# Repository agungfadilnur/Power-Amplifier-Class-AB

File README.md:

## Power Amplifier Class AB

This Drivers use SOCL (Super Output Capacitor Less) 506 and use 8 Pair Transistor for final output 

*Testing Video*

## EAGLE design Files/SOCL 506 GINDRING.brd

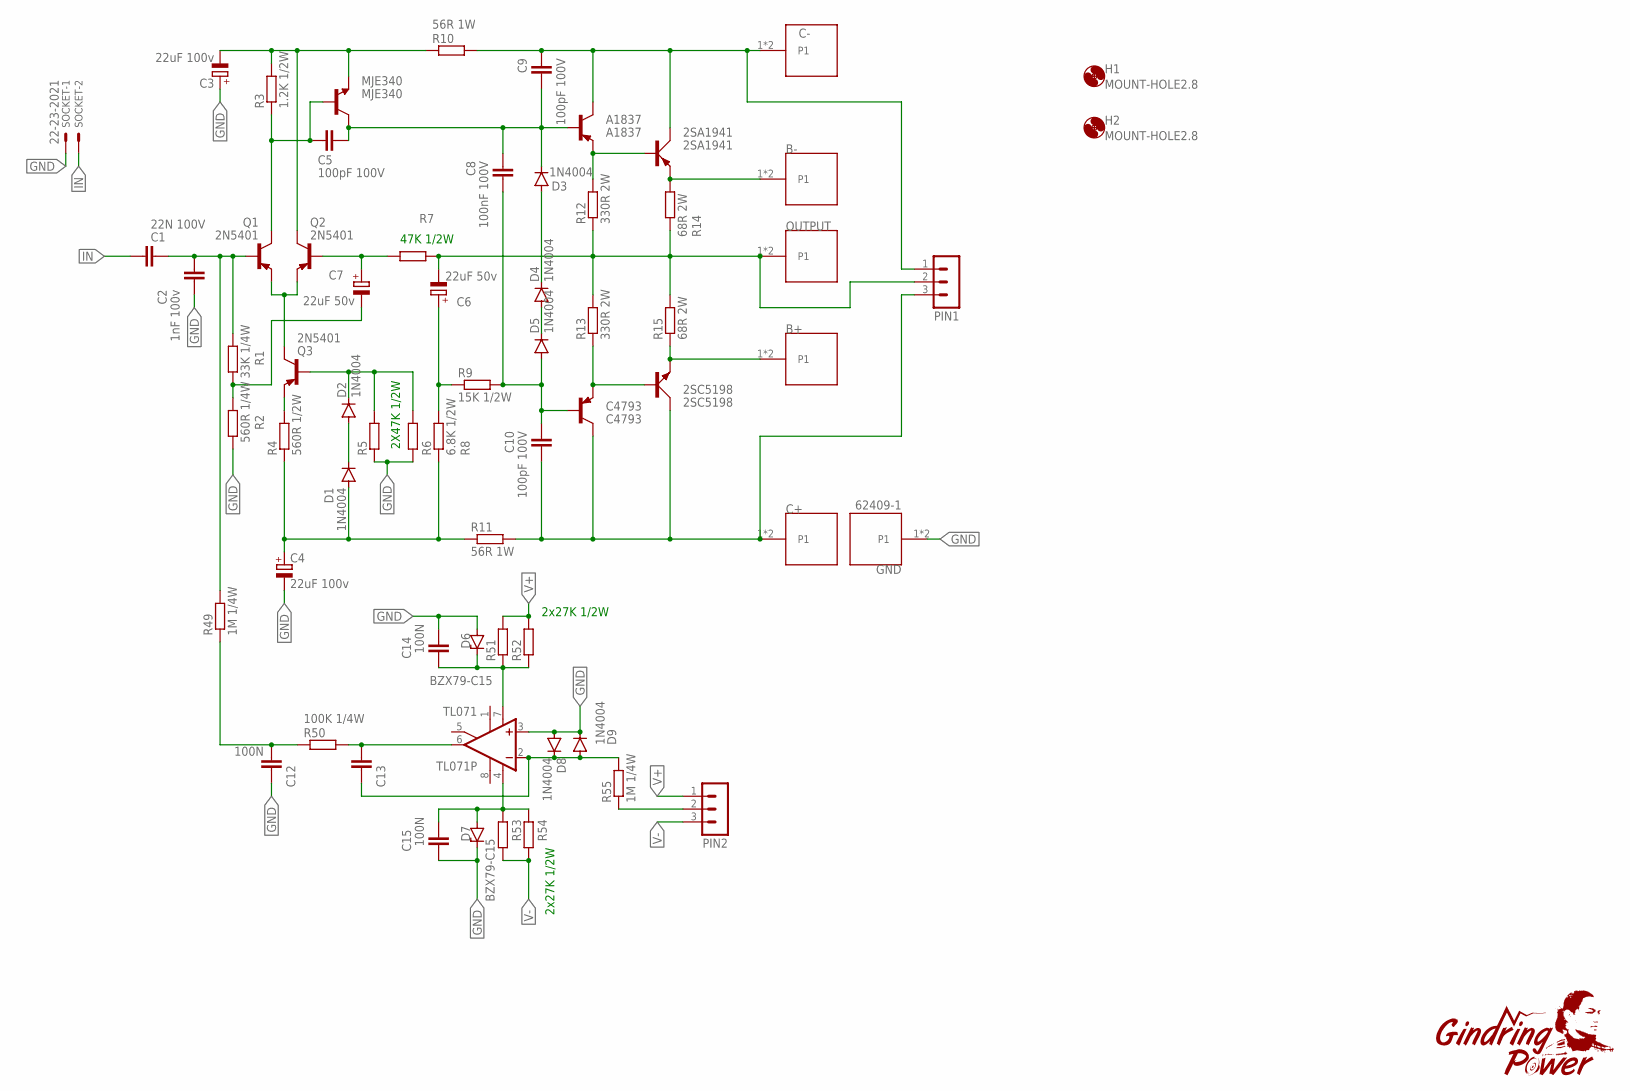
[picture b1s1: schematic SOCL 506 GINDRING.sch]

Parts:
2SA1941: 2SA1941; TOP3AV
2SC5198: 2SC5198; TOP3AV
A1837: A1837; TO220V
B+: 62409-1; TE_62409-1
B-: 62409-1; TE_62409-1
C1: 22N 100V; C5B2.5
C2: 1nF 100v; C5B2.5
C3, C4: 22uF 100v; E3,5-8
C5, C9, C10: 100pF 100V; C5B2.5
C6, C7: 22uF 50v; E2,5-6E
C8: 100nF 100V; C5B2.5
C12, C13, C14, C15: 100N; C5B2.5
C4793: C4793; TO220V
C+: 62409-1; TE_62409-1
C-: 62409-1; TE_62409-1
D1, D2, D3, D4, D5, D8, D9: 1N4004; DO41-10
D6, D7: BZX79-C15; DO41Z10
GND: 62409-1; TE_62409-1
H1, H2: MOUNT-HOLE2.8; 2,8
MJE340: MJE340; TO126
OUTPUT: 62409-1; TE_62409-1
PIN1, PIN2: MA03-1
Q1, Q2, Q3: 2N5401; TO92-CBE
R1: 33K 1/4W; 0207/10
R2: 560R 1/4W; 0207/10
R3: 1.2K 1/2W; 0207/15
R4: 560R 1/2W; 0207/15
R5, R6, R7, R51, R52, R53, R54: R-EU_0207/15; 0207/15
R8: 6.8K 1/2W; 0207/15
R9: 15K 1/2W; 0207/15
R10, R11: 56R 1W; 0207/15
R12, R13: 330R 2W; 0207/15
R14, R15: 68R 2W; 0207/15
R49, R55: 1M 1/4W; 0207/10
R50: 100K 1/4W; 0207/10
SOCKET: 22-23-2021
TL071: TL071P; DIL08

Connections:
GND: C2.2, C3.+, C4.-, C12.1, C14.2, C15.1, D6.A, D7.C, D8.A, D9.C, GND.1, GND.2, R2.1, R5.1, R6.1, SOCKET.1, TL071.3 (+IN)
IN: C1.1, SOCKET.2
unnamed: C1.2, C2.1, Q1.B, R1.2, R49.2
unnamed: Q1.E, Q2.E, Q3.C
unnamed: C5.1, MJE340.3 (B), Q1.C, R3.1
unnamed: C7.-, R1.1, R2.2
unnamed: C3.-, MJE340.1 (E), Q2.C, R3.2, R10.1
unnamed: Q3.E, R4.2
unnamed: D2.C, Q3.B, R5.2, R6.2
unnamed: D1.C, D2.A
unnamed: C4.+, D1.A, R4.1, R8.1, R11.1
unnamed: C7.+, Q2.B, R7.1
unnamed: 2SC5198.B, C4793.3 (E), R13.1
unnamed: C6.-, OUTPUT.1, OUTPUT.2, PIN1.2, R7.2, R12.1, R13.2, R14.1, R15.2
unnamed: C6.+, R8.2, R9.1
unnamed: C8.1, C10.2, C4793.1 (B), D5.A, R9.2
unnamed: 2SA1941.C, A1837.2 (C), C9.2, C-.1, C-.2, PIN1.1, R10.2
unnamed: A1837.1 (B), C5.2, C8.2, C9.1, D3.C, MJE340.2 (C)
unnamed: D3.A, D4.C
unnamed: D4.A, D5.C
unnamed: 2SC5198.C, C10.1, C4793.2 (C), C+.1, C+.2, PIN1.3, R11.2
unnamed: 2SA1941.B, A1837.3 (E), R12.2
unnamed: 2SA1941.E, B-.1, B-.2, R14.2
unnamed: C12.2, R49.1, R50.1
unnamed: 2SC5198.E, B+.1, B+.2, R15.1
unnamed: C14.1, D6.C, R51.1, R52.1, TL071.7 (V+)
unnamed: C13.1, D8.C, D9.A, R55.2, TL071.2 (-IN)
unnamed: C15.2, D7.A, R53.2, R54.2, TL071.4 (V-)
unnamed: C13.2, R50.2, TL071.6 (OUT)
unnamed: PIN2.2, R55.1
V+: PIN2.1, R51.2, R52.2
V-: PIN2.3, R53.1, R54.1

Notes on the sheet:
2X47K 1/2W
47K 1/2W
2x27K 1/2W

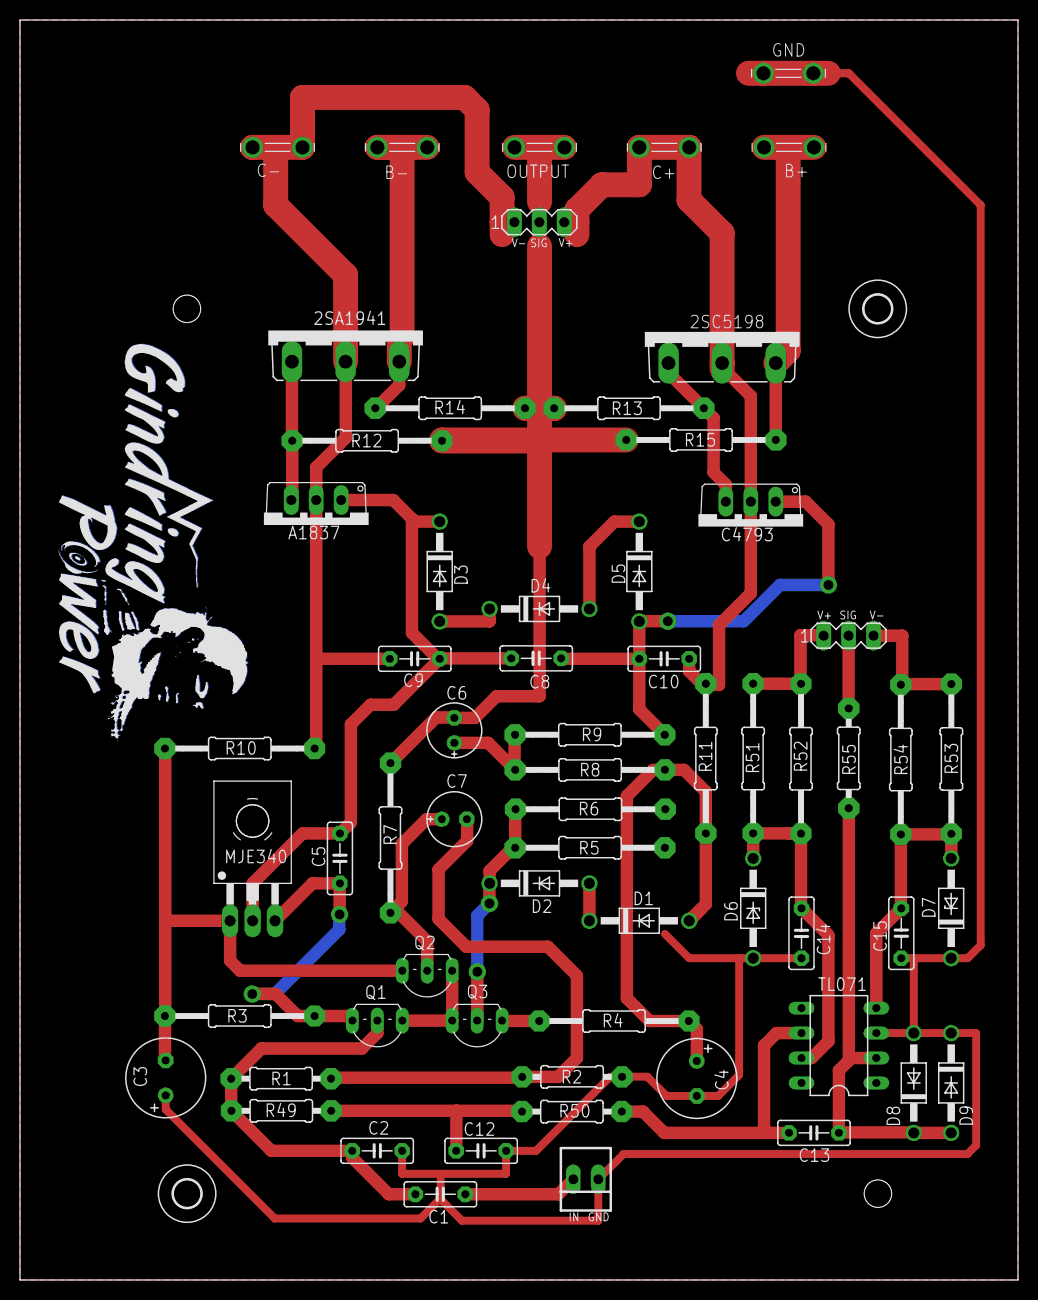
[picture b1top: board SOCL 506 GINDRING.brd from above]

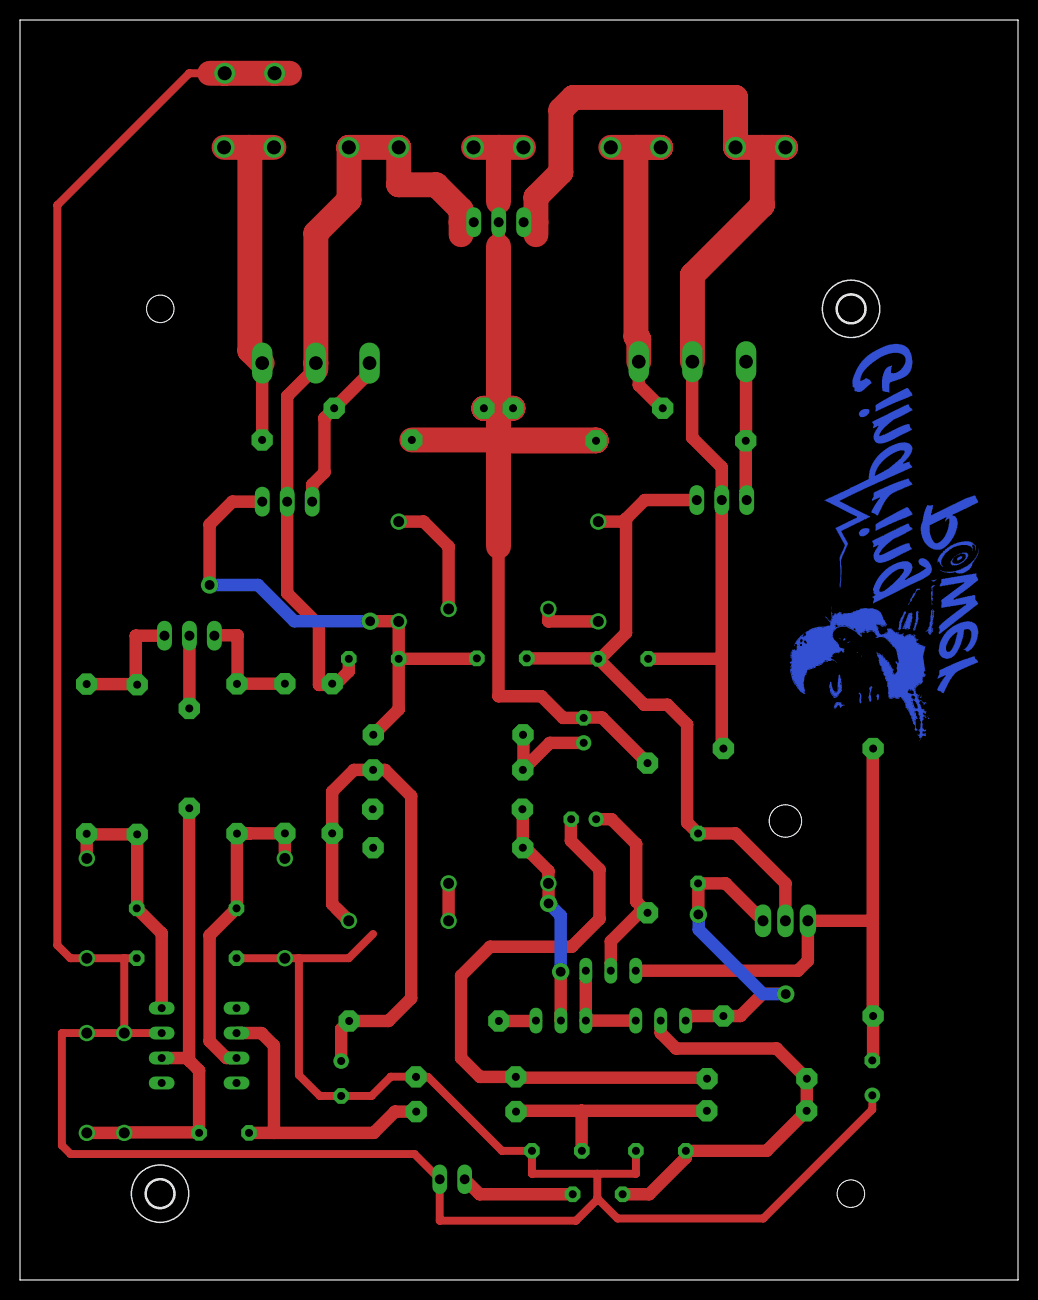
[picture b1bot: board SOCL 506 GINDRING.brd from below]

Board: 2 copper layers, 101.6 x 128.3 mm, 67 parts (2 on the bottom side), 32 nets.

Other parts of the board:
H5, H6: MOUNT-HOLE2.8; 2,8

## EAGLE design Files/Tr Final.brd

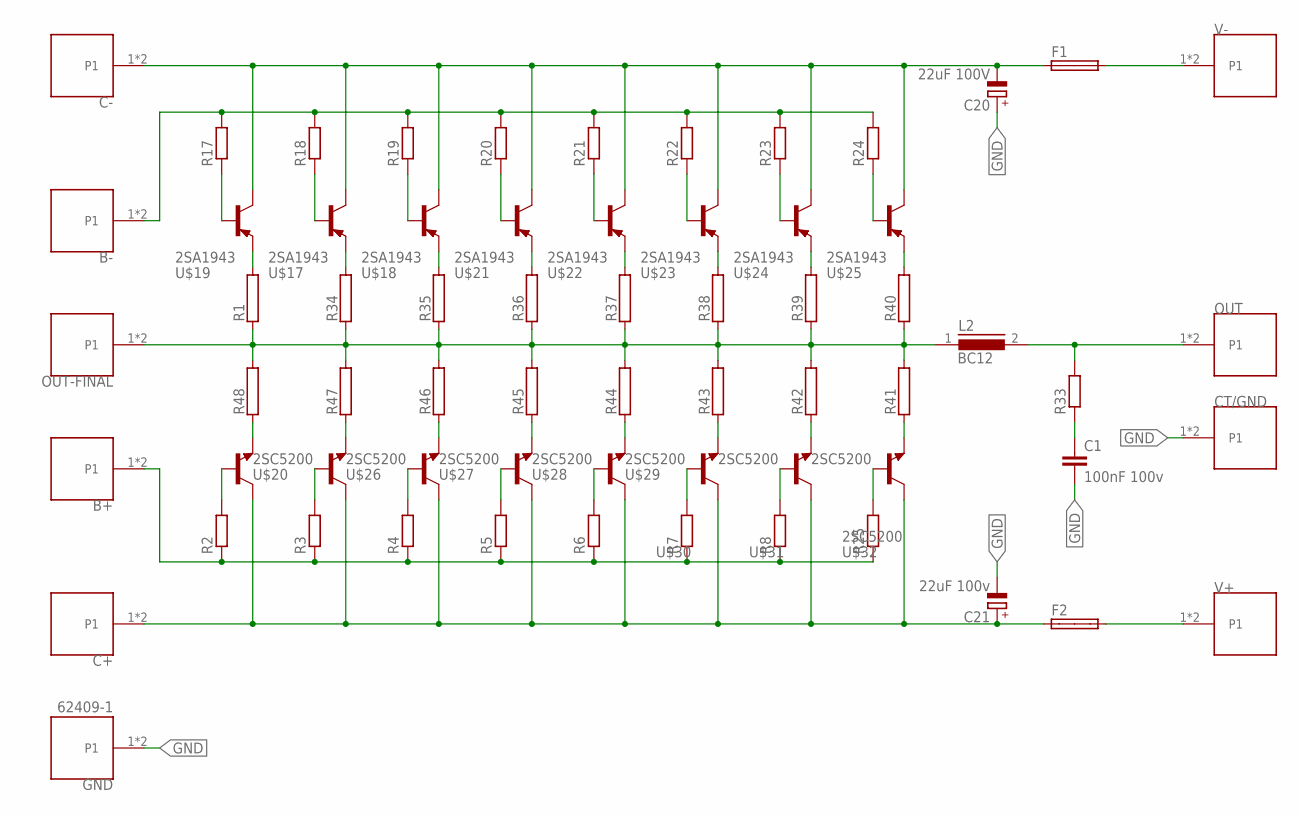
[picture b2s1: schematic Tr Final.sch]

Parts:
B+: 62409-1; TE_62409-1
B-: 62409-1; TE_62409-1
C1: 100nF 100v; C7.5B5
C20: 22uF 100V; E3,5-8
C21: 22uF 100v; E3,5-8
C+: 62409-1; TE_62409-1
C-: SKUN; TE_62409-1
CT/GND: 62409-1; TE_62409-1
F1, F2: SHK20L
GND: 62409-1; TE_62409-1
L2: BC12
OUT: 62409-1; TE_62409-1
OUT-FINAL: 62409-1; TE_62409-1
R1, R34, R35, R36, R37, R38, R39, R40, R41, R42, R43, R44, R45, R46, R47, R48: RMG100-V; TO-247-2V
R2, R3, R4, R5, R6, R7, R8, R17, R18, R19, R20, R21, R22, R23, R24, R25: R-EU_0207/15; 0207/15
R33: R-EU_0617/22; 0617/22
U$17, U$18, U$19, U$21, U$22, U$23, U$24, U$25: 2SA1943; TO-264
U$20, U$26, U$27, U$28, U$29, U$30, U$31, U$32: 2SC5200; TO-264
V+: 62409-1; TE_62409-1
V-: 62409-1; TE_62409-1

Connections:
GND: C1.2, C20.+, C21.-, CT/GND.1, CT/GND.2, GND.1, GND.2
unnamed: R17.1, U$19.B
unnamed: R18.1, U$17.B
unnamed: R19.1, U$18.B
unnamed: R20.1, U$21.B
unnamed: R21.1, U$22.B
unnamed: R22.1, U$23.B
unnamed: R23.1, U$24.B
unnamed: R24.1, U$25.B
unnamed: R1.2, U$19.E
unnamed: R34.2, U$17.E
unnamed: R35.2, U$18.E
unnamed: R36.2, U$21.E
unnamed: R37.2, U$22.E
unnamed: R38.2, U$23.E
unnamed: R39.2, U$24.E
unnamed: R40.2, U$25.E
unnamed: L2.1, OUT-FINAL.1, OUT-FINAL.2, R1.1, R34.1, R35.1, R36.1, R37.1, R38.1, R39.1, R40.1, R41.2, R42.2, R43.2, R44.2, R45.2, R46.2, R47.2, R48.2
unnamed: L2.2, OUT.1, OUT.2, R33.2
unnamed: C20.-, C-.1, C-.2, F1.1A, U$17.C, U$18.C, U$19.C, U$21.C, U$22.C, U$23.C, U$24.C, U$25.C
unnamed: F2.2A, V+.1, V+.2
unnamed: F1.2A, V-.1, V-.2
unnamed: C1.1, R33.1
unnamed: R48.1, U$20.E
unnamed: R47.1, U$26.E
unnamed: R46.1, U$27.E
unnamed: R45.1, U$28.E
unnamed: R44.1, U$29.E
unnamed: R43.1, U$30.E
unnamed: R42.1, U$31.E
unnamed: R41.1, U$32.E
unnamed: R2.2, U$20.B
unnamed: R3.2, U$26.B
unnamed: R4.2, U$27.B
unnamed: R5.2, U$28.B
unnamed: R6.2, U$29.B
unnamed: R7.2, U$30.B
unnamed: R8.2, U$31.B
unnamed: R25.2, U$32.B
unnamed: C21.+, C+.1, C+.2, F2.1A, U$20.C, U$26.C, U$27.C, U$28.C, U$29.C, U$30.C, U$31.C, U$32.C
unnamed: B-.1, B-.2, R17.2, R18.2, R19.2, R20.2, R21.2, R22.2, R23.2, R24.2
unnamed: B+.1, B+.2, R2.1, R3.1, R4.1, R5.1, R6.1, R7.1, R8.1, R25.1

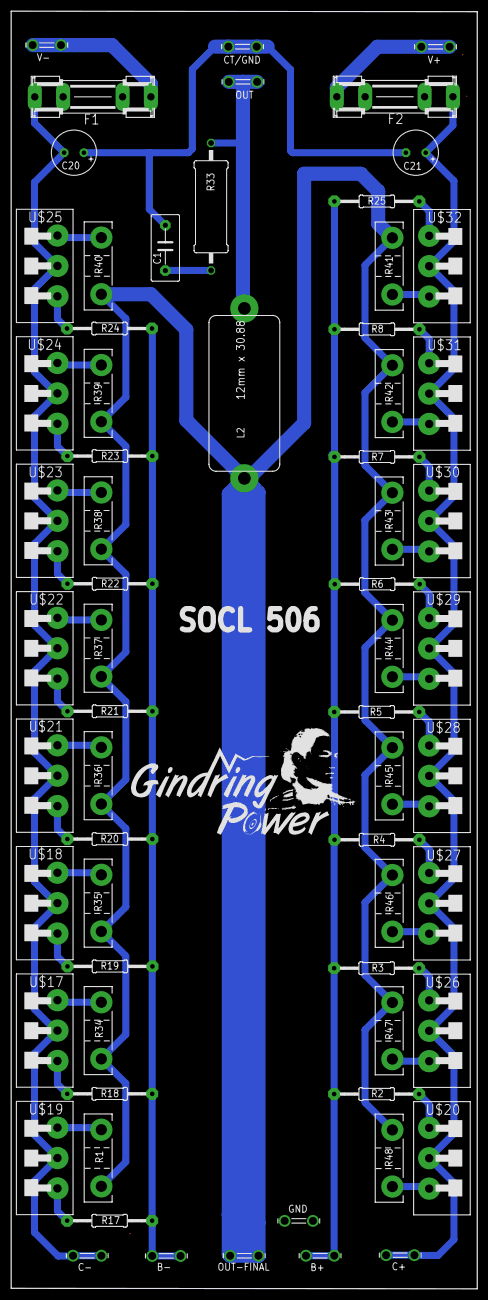
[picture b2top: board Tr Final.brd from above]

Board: 2 copper layers, 83.6 x 229.2 mm, 65 parts (0 on the bottom side), 42 nets.
